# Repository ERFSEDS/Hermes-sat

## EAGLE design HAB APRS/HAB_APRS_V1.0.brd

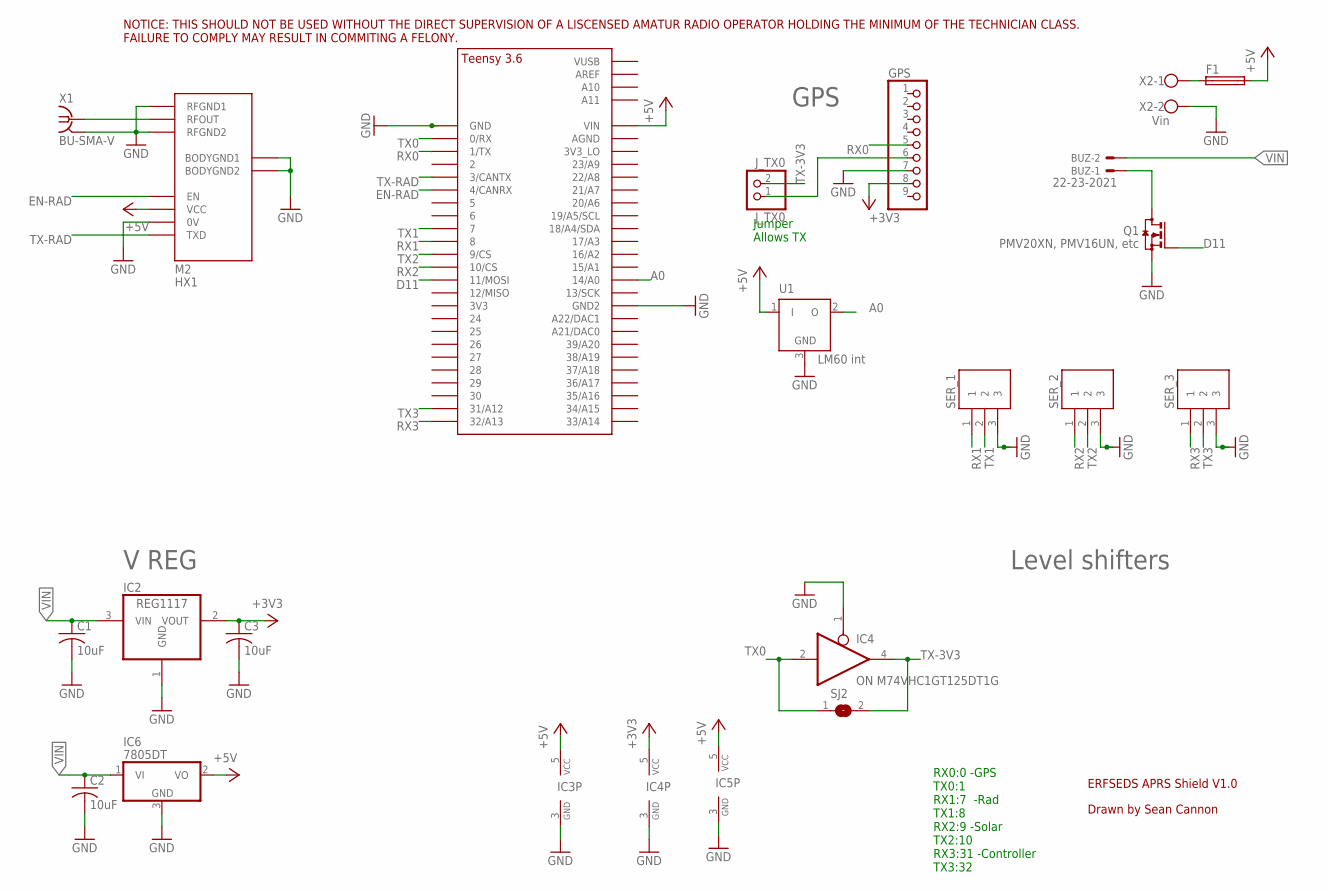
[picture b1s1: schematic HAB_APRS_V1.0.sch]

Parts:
BUZ: 22-23-2021
C1, C2, C3: 10uF; C0805
F1: FUSE_CHIP(6126-METRIC); FUSC6126X294N
GPS: PINHD-1X9; 1X09-BIG
IC2: REG1117; SOT223
IC3, IC4, IC5: ON M74VHC1GT125DT1G; SOT23-5
IC6: 7805DT; TO252
J_TX0: J_TX0; 1X02
M2: HX1
Q1: PMV20XN, PMV16UN, etc; SOT23
SER_1, SER_2, SER_3: MOLEX_SL_03-70551; SL_70551_3
SJ2: SJ
U1: LM60 int; TO92
U$1: TEENSY_3.5/3.6_BASIC
X1: BU-SMA-V
X2: Vin; W237-102

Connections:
+3V3: C3.1, GPS.8, IC2.2 (VOUT), IC4.5 (VCC)
+5V: F1.2, IC3.5 (VCC), IC5.5 (VCC), IC6.2 (VO), M2.VCC, U1.1 (I), U$1.VIN
A0: U1.2 (O), U$1.14/A0
D11: Q1.1 (G), U$1.11/MOSI
EN-RAD: M2.EN, U$1.4/CANRX
GND: C1.2, C2.2, C3.2, GPS.7, IC2.1 (GND), IC3.3 (GND), IC4.1 (OE), IC4.3 (GND), IC5.3 (GND), IC6.3 (GND), M2.0V, M2.BODYGND1, M2.BODYGND2, M2.RFGND1, M2.RFGND2, Q1.2 (S), SER_1.3, SER_2.3, SER_3.3, U1.3 (GND), U$1.GND, U$1.GND2, X1.2 (GND), X1.3 (GND), X1.4 (GND), X1.5 (GND), X2.2
unnamed: BUZ.1, Q1.3 (D)
unnamed: GPS.6, J_TX0.1
unnamed: F1.1, X2.1
RFOUT: M2.RFOUT, X1.1
RX0: GPS.5, U$1.1/TX
RX1: SER_1.1, U$1.8
RX2: SER_2.1, U$1.10/CS
RX3: SER_3.1, U$1.32/A13
TX0: IC4.2 (I), SJ2.1, U$1.0/RX
TX1: SER_1.2, U$1.7
TX2: SER_2.2, U$1.9/CS
TX3: SER_3.2, U$1.31/A12
TX-3V3: IC4.4 (O), J_TX0.2, SJ2.2
TX-RAD: M2.TXD, U$1.3/CANTX
VIN: BUZ.2, C1.1, C2.1, IC2.3 (VIN), IC6.1 (VI)

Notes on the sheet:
V REG
Level shifters
GPS
Drawn by Sean Cannon
ERFSEDS APRS Shield V1.0
NOTICE: THIS SHOULD NOT BE USED WITHOUT THE DIRECT SUPERVISION OF A LISCENSED AMATUR RADIO OPERATOR HOLDING THE MINIMUM OF THE TECHNICIAN CLASS. FAILURE TO COMPLY MAY RESULT IN COMMITING A FELONY.
RX0:0 -GPS TX0:1 RX1:7 -Rad TX1:8 RX2:9 -Solar TX2:10 RX3:31 -Controller TX3:32
Jumper Allows TX

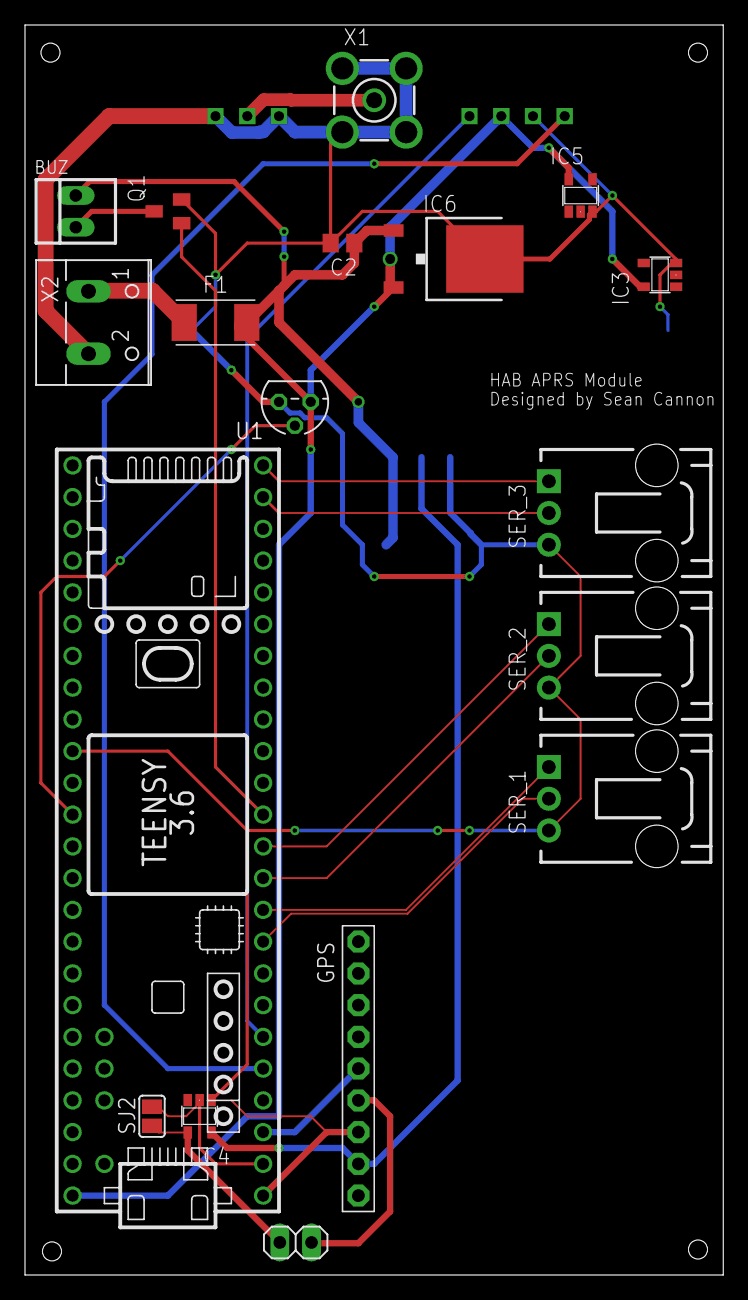
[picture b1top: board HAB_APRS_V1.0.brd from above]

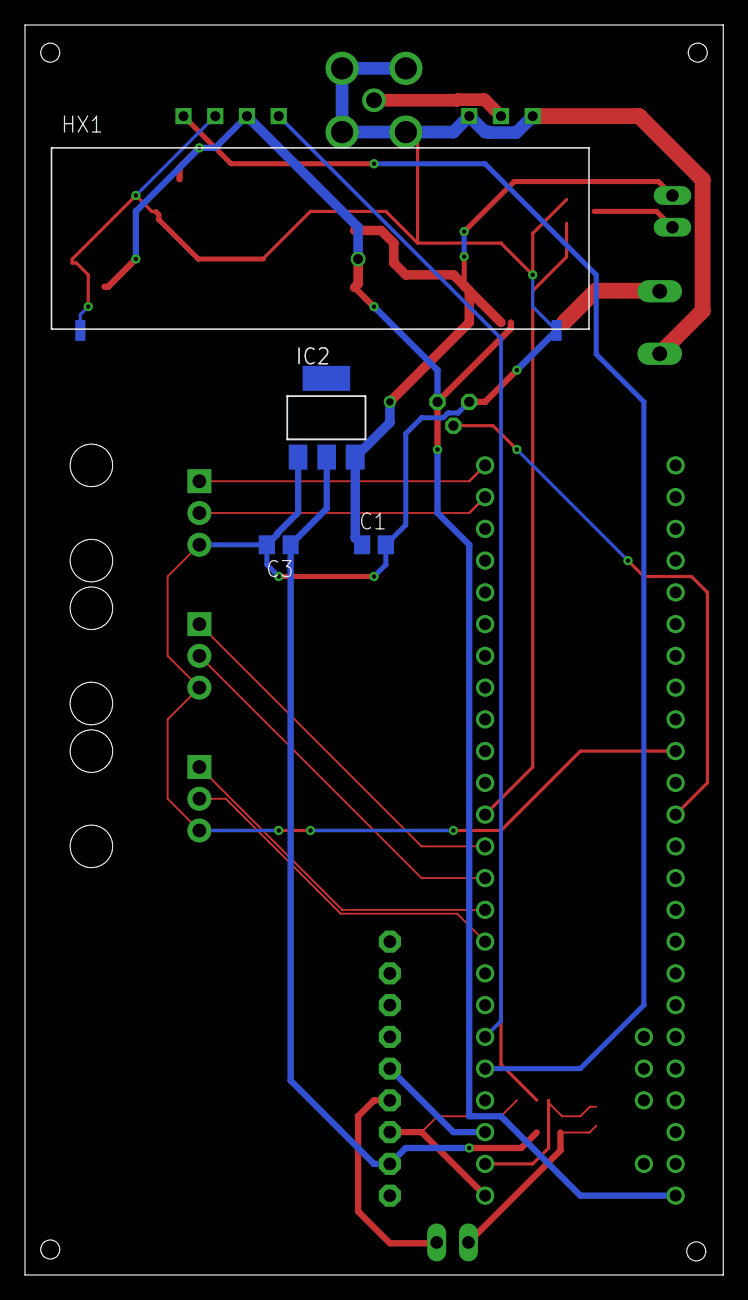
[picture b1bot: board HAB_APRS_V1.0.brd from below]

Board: 2 copper layers, 55.9 x 100.0 mm, 22 parts (4 on the bottom side), 21 nets.

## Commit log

2020-10-21 Added APRS PCB Files
    These are 99% complete. They just need to have anesthetics changed
